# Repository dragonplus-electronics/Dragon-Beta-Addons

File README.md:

# Dragon-Beta Add-ons
Add-on boards by Phill Harvey-Smith for ease of use and construction today.

## Background
The Dragon Beta was a machine in development at the time of Dragon Data's demise in 1984. Only three boards are known to have existed - and only one can be located now. The one board which remains is in the care of the Dragon Data archive at http://www.dragondata.co.uk. It is this latter board which has formed the basis for this current reverse engineering project. Richard, from the Dragon Data archive had made some very clear photographs of his Dragon Beta board before, during and after it's restoration. That board was returned to working order, but understandably Richard was not keen to continually use such a rare piece of computing history. The board was apparently rescued by the Dragon Data M.D. as he left the building for the final time. The Dragon Beta disks were still held by Duncan Smeed of 'Inside the Dragon' fame, and he supplied those to Richard for imaging.

## Improvements and Addons

Many of the components used on the Dragon Beta are obsolete - to the point of being almost unobtainable. Phill has gone to great lengths to create some good add-on boards which can be used to replace the archaic SRAM chips that handle paging, as well as replacing the 32 DRAM chips which provided the original 256K. These are replaced by a small daughterboard. He has also created a 512KB expansion RAM which plugs into the expansion port and effectively takes the machine to 768K of RAM.

Another archaic part of the Beta was its use of the original Sony 26-pin floppy drive connector. This is different to the Amstrad 26-pin connector. Phill has put together a 26-pin to 34-pin adapter, which allows the connection of normal floppy disk drives.

The last area for now is improvements to the keyboard interface. The original Dragon Beta used a matrix scanned/bit serialised keyboard. As with many other old machines, Phill put together a PS/2 keyboard adapter, and in addition now has a USB keyboard and mouse adapter (yes, the Dragon Beta had a mouse - it also had a light pen - but we will likely leave that back in 1984!)

## Disclaimer

These boards have been built and tested and proven to work so far as testing that has been carried out has shown. No warranty is given regarding the suitability or reliability of these boards, and as such, they are supplied as-is for your enjoyment. Any feedback is always welcome.

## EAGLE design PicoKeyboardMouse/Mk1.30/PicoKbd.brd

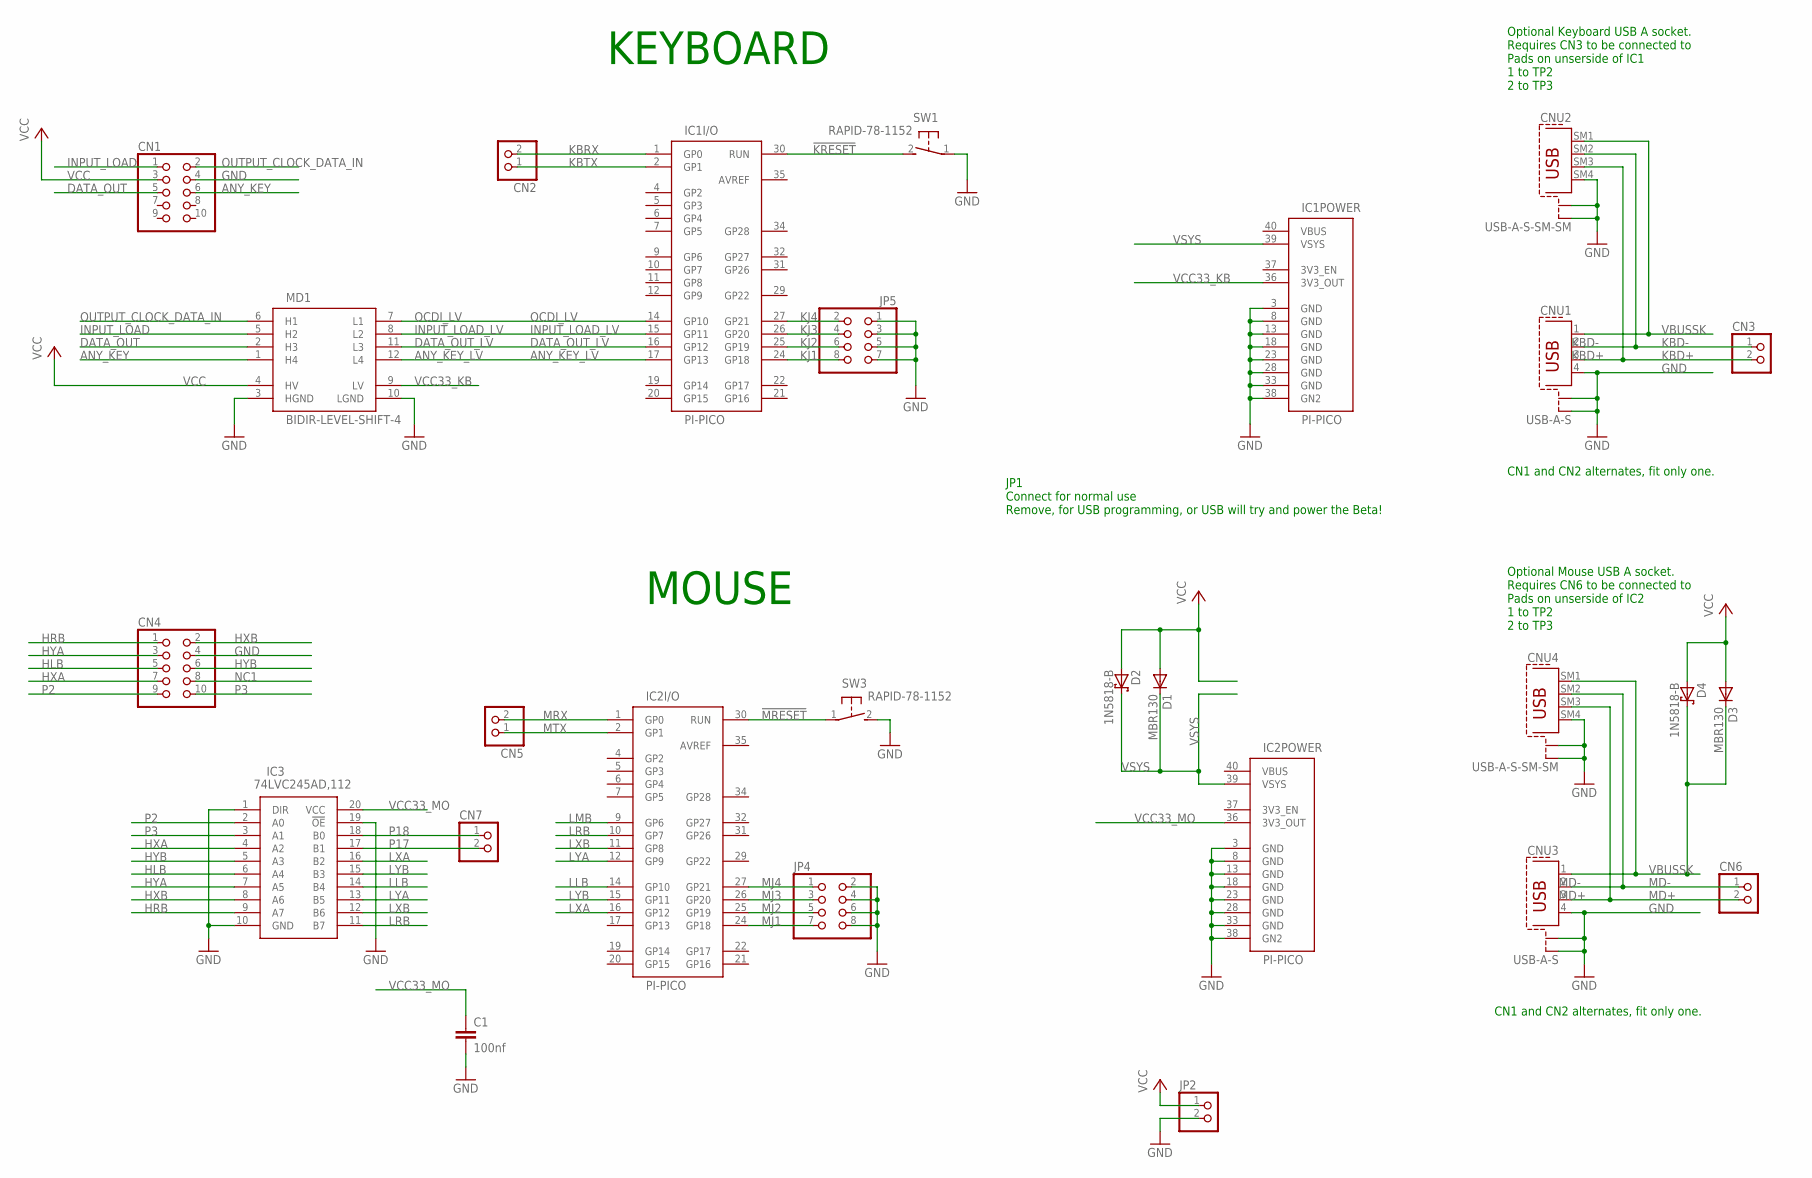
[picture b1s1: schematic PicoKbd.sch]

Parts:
C1: 100nf; C025-025X050
CN1, CN4: PINHD-2X5/90; 2X05/90
CN2, CN3, CN5, CN6, CN7: PINHD-1X2; 1X02
CNU1, CNU3: USB-A-S; USB-A-SHIELD-PTH
CNU2, CNU4: USB-A-S-SM-SM; USB-A-SHIELD-SM
D1, D3: MBR130; SOD123
D2, D4: 1N5818-B; DO41-7.6
IC1, IC2: PI-PICO; PI-PICO-MAIN
IC3: 74LVC245AD,112; SOIC127P1032X265-20N
JP2: PINHD-1X2/90; 1X02/90
JP4, JP5: PINHD-2X4; 2X04
MD1: BIDIR-LEVEL-SHIFT-4; BIDIR-LEVEL-SHIFT
SW1, SW3: RAPID-78-1152; B3F-31XX

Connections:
!KRESET: IC1.30 (RUN), SW1.2 (S)
!MRESET: IC2.30 (RUN), SW3.1
ANY_KEY: CN1.6, MD1.1 (H4)
ANY_KEY_LV: IC1.17 (GP13), MD1.12 (L4)
DATA_OUT: CN1.5, MD1.2 (H3)
DATA_OUT_LV: IC1.16 (GP12), MD1.11 (L3)
GND: C1.2, CN1.4, CN4.4, CNU1.4, CNU1.S1, CNU1.S2, CNU2.S1, CNU2.S2, CNU2.SM4 (4), CNU3.4, CNU3.S1, CNU3.S2, CNU4.S1, CNU4.S2, CNU4.SM4 (4), IC1.3 (GND), IC1.8 (GND), IC1.13 (GND), IC1.18 (GND), IC1.23 (GND), IC1.28 (GND), IC1.33 (GND), IC1.38 (GN2), IC2.3 (GND), IC2.8 (GND), IC2.13 (GND), IC2.18 (GND), IC2.23 (GND), IC2.28 (GND), IC2.33 (GND), IC2.38 (GN2), IC3.1 (DIR), IC3.10 (GND), IC3.19 (!OE), JP2.2, JP4.2, JP4.4, JP4.6, JP4.8, JP5.1, JP5.3, JP5.5, JP5.7, MD1.3 (HGND), MD1.10 (LGND), SW1.1, SW3.2 (S)
HLB: CN4.5, IC3.6 (A4)
HRB: CN4.1, IC3.9 (A7)
HXA: CN4.7, IC3.4 (A2)
HXB: CN4.2, IC3.8 (A6)
HYA: CN4.3, IC3.7 (A5)
HYB: CN4.6, IC3.5 (A3)
INPUT_LOAD: CN1.1, MD1.5 (H2)
INPUT_LOAD_LV: IC1.15 (GP11), MD1.8 (L2)
KBD+: CN3.2, CNU1.3, CNU2.SM3 (3)
KBD-: CN3.1, CNU1.2, CNU2.SM2 (2)
KBRX: CN2.2, IC1.1 (GP0)
KBTX: CN2.1, IC1.2 (GP1)
KJ1: IC1.24 (GP18), JP5.8
KJ2: IC1.25 (GP19), JP5.6
KJ3: IC1.26 (GP20), JP5.4
KJ4: IC1.27 (GP21), JP5.2
LLB: IC2.14 (GP10), IC3.14 (B4)
LMB: IC2.9 (GP6)
LRB: IC2.10 (GP7), IC3.11 (B7)
LXA: IC2.16 (GP12), IC3.16 (B2)
LXB: IC2.11 (GP8), IC3.12 (B6)
LYA: IC2.12 (GP9), IC3.13 (B5)
LYB: IC2.15 (GP11), IC3.15 (B3)
MD+: CN6.2, CNU3.3, CNU4.SM3 (3)
MD-: CN6.1, CNU3.2, CNU4.SM2 (2)
MJ1: IC2.24 (GP18), JP4.7
MJ2: IC2.25 (GP19), JP4.5
MJ3: IC2.26 (GP20), JP4.3
MJ4: IC2.27 (GP21), JP4.1
MRX: CN5.2, IC2.1 (GP0)
MTX: CN5.1, IC2.2 (GP1)
NC1: CN4.8
OCDI_LV: IC1.14 (GP10), MD1.7 (L1)
OUTPUT_CLOCK_DATA_IN: CN1.2, MD1.6 (H1)
P2: CN4.9, IC3.2 (A0)
P3: CN4.10, IC3.3 (A1)
P17: CN7.2, IC3.17 (B1)
P18: CN7.1, IC3.18 (B0)
VBUSSK: CNU1.1, CNU2.SM1 (1), CNU3.1, CNU4.SM1 (1), D3.C, D4.C
VCC: CN1.3, D1.A, D2.A, D3.A, D4.A, JP2.1, MD1.4 (HV)
VCC33_KB: IC1.36 (3V3_OUT), MD1.9 (LV)
VCC33_MO: C1.1, IC2.36 (3V3_OUT), IC3.20 (VCC)
VSYS: D1.C, D2.C, IC1.39 (VSYS), IC2.39 (VSYS)

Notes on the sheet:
JP1 Connect for normal use Remove, for USB programming, or USB will try and power the Beta!
KEYBOARD
MOUSE
CN1 and CN2 alternates, fit only one.
Optional Keyboard USB A socket. Requires CN3 to be connected to Pads on unserside of IC1 1 to TP2 2 to TP3
Optional Mouse USB A socket. Requires CN6 to be connected to Pads on unserside of IC2 1 to TP2 2 to TP3

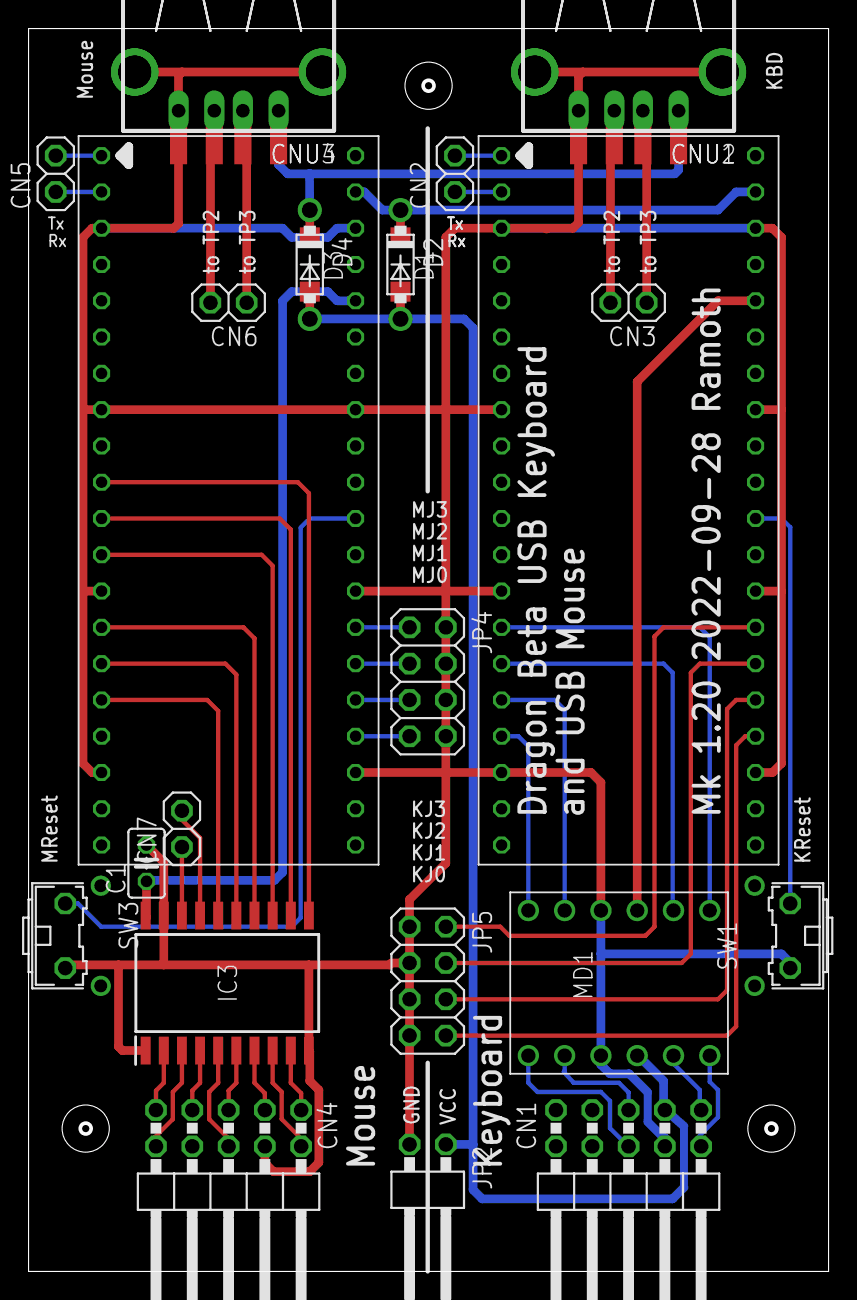
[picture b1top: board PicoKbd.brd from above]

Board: 2 copper layers, 55.7 x 86.7 mm, 28 parts (0 on the bottom side), 48 nets.

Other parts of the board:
U$1, U$3, U$4: STAND-OFF

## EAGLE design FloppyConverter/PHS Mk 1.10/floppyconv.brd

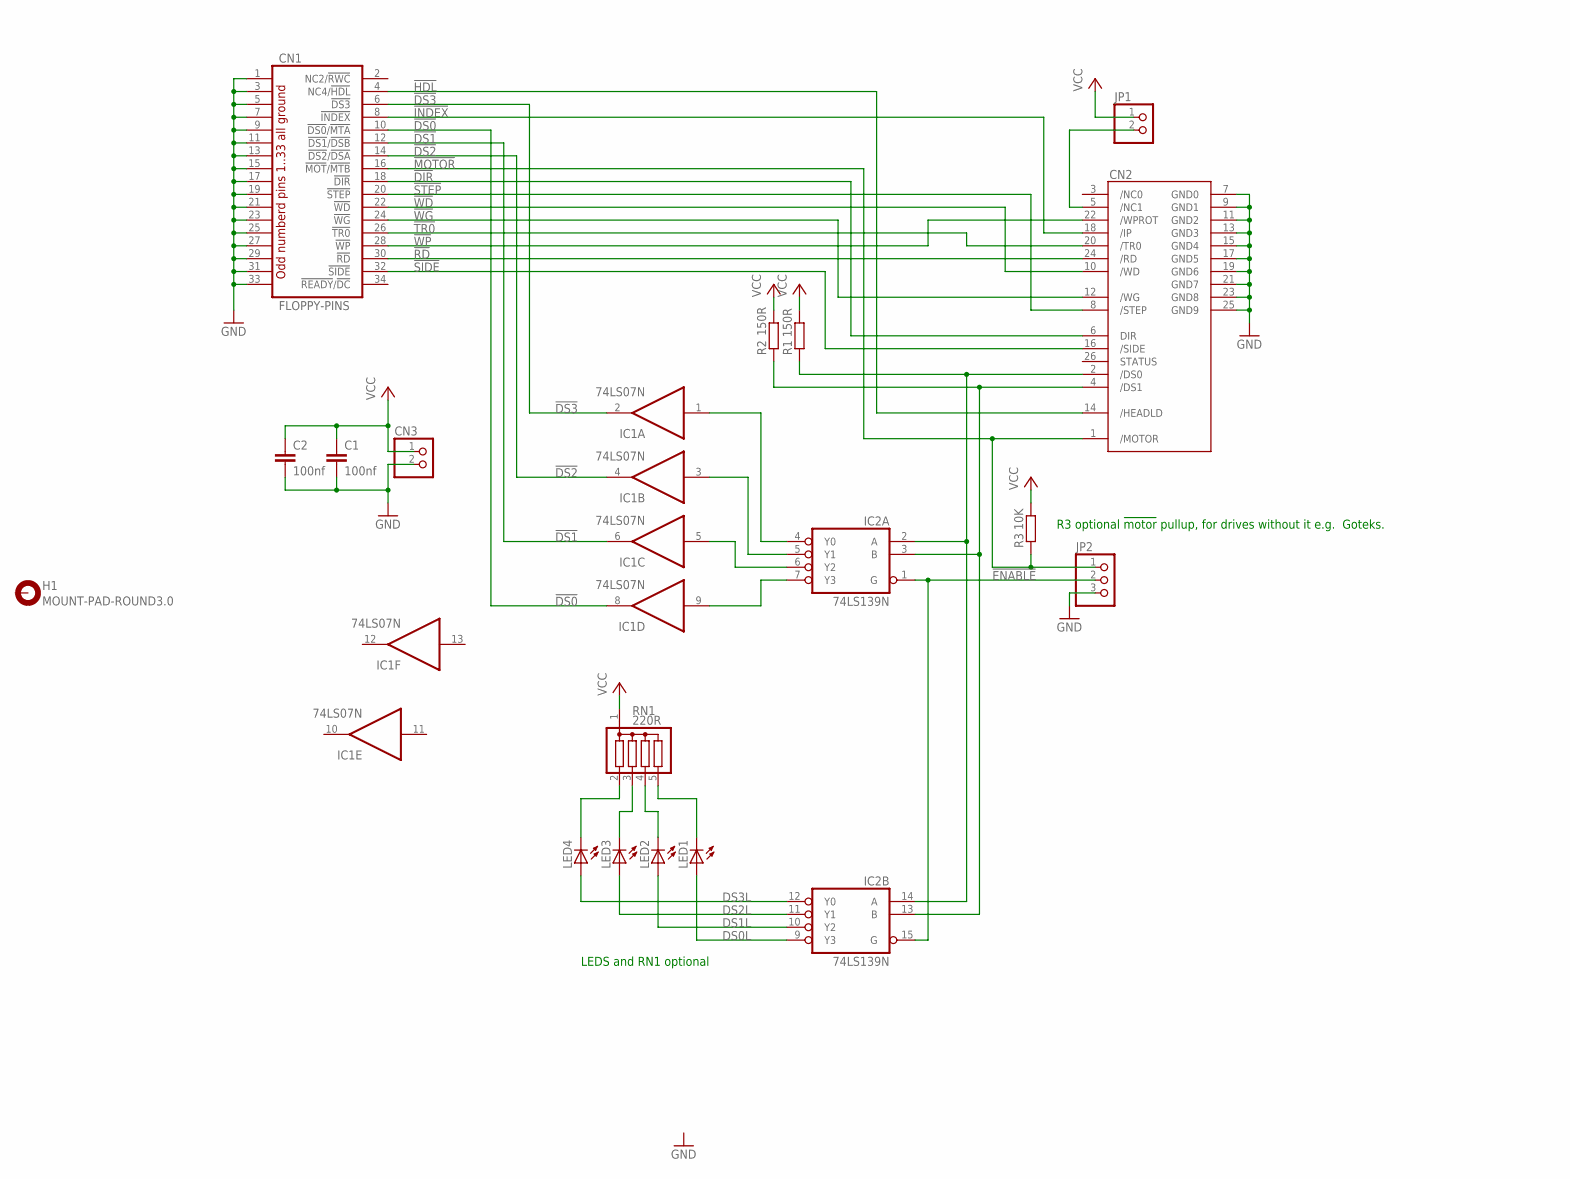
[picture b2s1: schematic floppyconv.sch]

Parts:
C1, C2: 100nf; C025-025X050
CN1: FLOPPY-PINS
CN2: DRAGON-BETA-FLOPPY; 2X13
CN3: PINHD-1X2; 1X02
H1: MOUNT-PAD-ROUND3.0; 3,0-PAD
IC1: 74LS07N; DIL14
IC2: 74LS139N; DIL16
JP1: PINHD-1X2; 1X02
JP2: PINHD-1X3; 1X03
LED1, LED2, LED3, LED4: LED3MM
R1, R2: 150R; 0207/10
R3: 10K; 0207/10
RN1: 220R; SIL5R

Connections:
!BDS0: CN2.2 (/DS0), IC2.2 (A), IC2.14 (A), R1.1
!BDS1: CN2.4 (/DS1), IC2.3 (B), IC2.13 (B), R2.1
!DIR: CN1.18 (!DIR), CN2.6 (DIR)
!DS0: CN1.10 (!DS0!/!MTA), IC1.8 (O)
!DS1: CN1.12 (!DS1!/!DSB), IC1.6 (O)
!DS2: CN1.14 (!DS2!/!DSA), IC1.4 (O)
!DS3: CN1.6 (!DS3), IC1.2 (O)
!ENABLE: IC2.1 (G), IC2.15 (G), JP2.2
!HDL: CN1.4 (NC4/!HDL), CN2.14 (/HEADLD)
!INDEX: CN1.8 (!INDEX), CN2.18 (/IP)
!MOTOR: CN1.16 (!MOT!/!MTB), CN2.1 (/MOTOR), JP2.1, R3.1
!RD: CN1.30 (!RD), CN2.24 (/RD)
!SIDE: CN1.32 (!SIDE), CN2.16 (/SIDE)
!STEP: CN1.20 (!STEP), CN2.8 (/STEP)
!TR0: CN1.26 (!TR0), CN2.20 (/TR0)
!WD: CN1.22 (!WD), CN2.10 (/WD)
!WG: CN1.24 (!WG), CN2.12 (/WG)
!WP: CN1.28 (!WP), CN2.22 (/WPROT)
DS0L: IC2.9 (Y3), LED1.A
DS1L: IC2.10 (Y2), LED2.A
DS2L: IC2.11 (Y1), LED3.A
DS3L: IC2.12 (Y0), LED4.A
GND: C1.2, C2.2, CN1.1 (GND), CN1.3 (GND), CN1.5 (GND), CN1.7 (GND), CN1.9 (GND), CN1.11 (GND), CN1.13 (GND), CN1.15 (GND), CN1.17 (GND), CN1.19 (GND), CN1.21 (GND), CN1.23 (GND), CN1.25 (GND), CN1.27 (GND), CN1.29 (GND), CN1.31 (GND), CN1.33 (GND), CN2.7 (GND0), CN2.9 (GND1), CN2.11 (GND2), CN2.13 (GND3), CN2.15 (GND4), CN2.17 (GND5), CN2.19 (GND6), CN2.21 (GND7), CN2.23 (GND8), CN2.25 (GND9), CN3.2, IC1.7 (GND), IC2.8 (GND), JP2.3
unnamed: IC1.1 (I), IC2.4 (Y0)
unnamed: IC1.3 (I), IC2.5 (Y1)
unnamed: IC1.5 (I), IC2.6 (Y2)
unnamed: IC1.9 (I), IC2.7 (Y3)
unnamed: LED1.K (C), RN1.5
unnamed: LED2.K (C), RN1.4
unnamed: LED3.K (C), RN1.3
unnamed: LED4.K (C), RN1.2
unnamed: CN2.5 (/NC1), JP1.2
VCC: C1.1, C2.1, CN3.1, IC1.14 (VCC), IC2.16 (VCC), JP1.1, R1.2, R2.2, R3.2, RN1.1

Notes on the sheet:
LEDS and RN1 optional
R3 optional !motor! pullup, for drives without it e.g. Goteks.

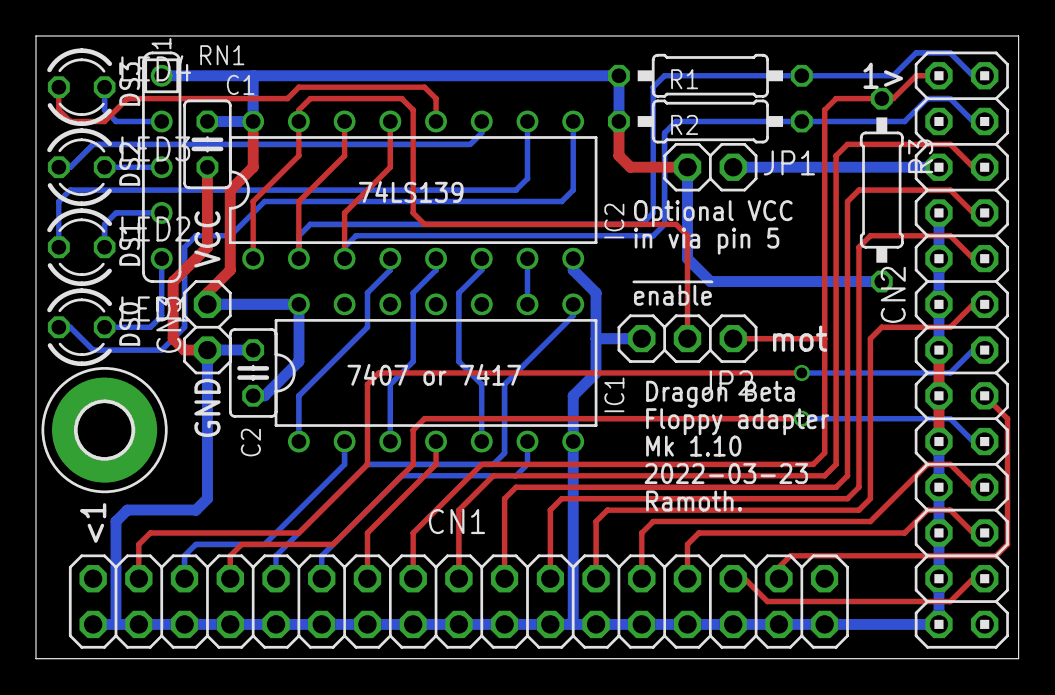
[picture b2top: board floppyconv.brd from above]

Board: 2 copper layers, 54.6 x 34.6 mm, 18 parts (0 on the bottom side), 33 nets.

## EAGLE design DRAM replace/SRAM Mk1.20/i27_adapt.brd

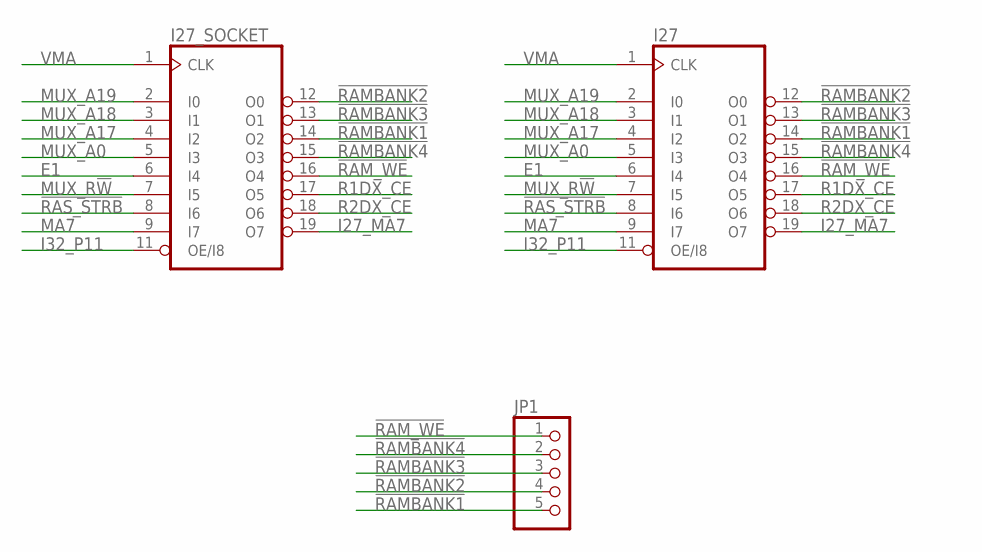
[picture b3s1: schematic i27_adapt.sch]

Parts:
I27, I27_SOCKET: 16V8-ROUND; DIL20-R
JP1: PINHD-1X5/90; 1X05/90

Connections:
!RAMBANK1: I27.14 (O2), I27_SOCKET.14 (O2), JP1.5
!RAMBANK2: I27.12 (O0), I27_SOCKET.12 (O0), JP1.4
!RAMBANK3: I27.13 (O1), I27_SOCKET.13 (O1), JP1.3
!RAMBANK4: I27.15 (O3), I27_SOCKET.15 (O3), JP1.2
!RAM_WE: I27.16 (O4), I27_SOCKET.16 (O4), JP1.1
!RAS_STRB: I27.8 (I6), I27_SOCKET.8 (I6)
E1: I27.6 (I4), I27_SOCKET.6 (I4)
GND: I27.10 (GND), I27_SOCKET.10 (GND)
I27_MA7: I27.19 (O7), I27_SOCKET.19 (O7)
I32_P11: I27.11 (OE/I8), I27_SOCKET.11 (OE/I8)
MA7: I27.9 (I7), I27_SOCKET.9 (I7)
MUX_A0: I27.5 (I3), I27_SOCKET.5 (I3)
MUX_A17: I27.4 (I2), I27_SOCKET.4 (I2)
MUX_A18: I27.3 (I1), I27_SOCKET.3 (I1)
MUX_A19: I27.2 (I0), I27_SOCKET.2 (I0)
MUX_R!W!: I27.7 (I5), I27_SOCKET.7 (I5)
R1DX_CE: I27.17 (O5), I27_SOCKET.17 (O5)
R2DX_CE: I27.18 (O6), I27_SOCKET.18 (O6)
VCC: I27.20 (VCC), I27_SOCKET.20 (VCC)
VMA: I27.1 (CLK), I27_SOCKET.1 (CLK)

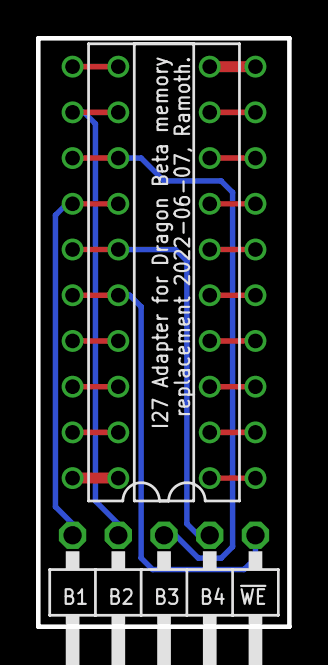
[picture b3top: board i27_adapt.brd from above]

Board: 2 copper layers, 13.9 x 32.7 mm, 3 parts (0 on the bottom side), 20 nets.

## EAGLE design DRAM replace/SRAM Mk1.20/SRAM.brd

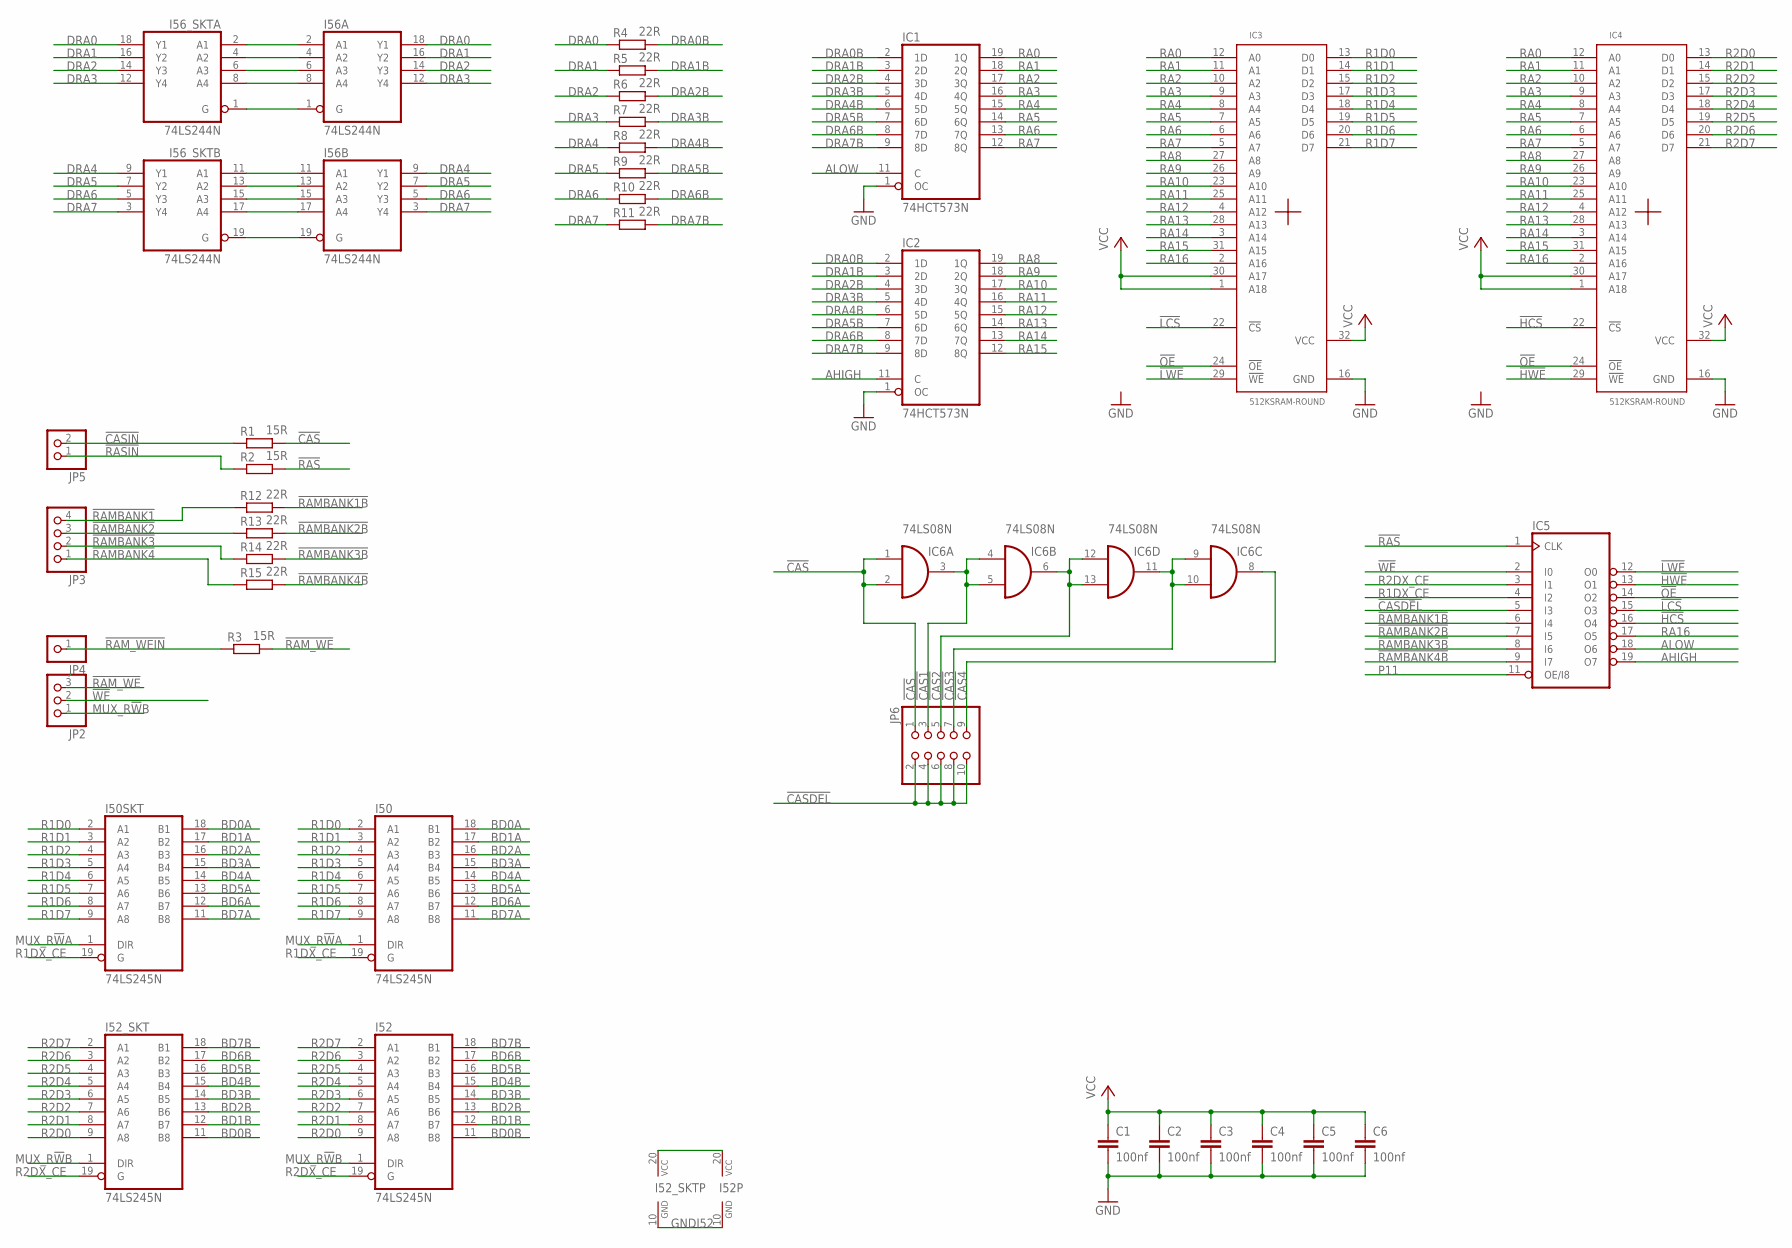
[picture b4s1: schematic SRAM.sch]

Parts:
C1, C2, C3, C4, C5, C6: 100nf; C025-025X050
I50, I50SKT, I52, I52_SKT: 74LS245N; DIL20
I56, I56_SKT: 74LS244N; DIL20
IC1, IC2: 74HCT573N; DIL20
IC3, IC4: 512KSRAM-ROUND; DIL32-ROUND
IC5: 16V8-ROUND; DIL20-R
IC6: 74LS08N; DIL14
JP2: PINHD-1X3; 1X03
JP3: PINHD-1X4; 1X04
JP4: PINHD-1X1; 1X01
JP5: PINHD-1X2; 1X02
JP6: PINHD-2X5; 2X05
R1, R2, R3: 15R; 0204/5
R4, R5, R6, R7, R8, R9, R10, R11, R12, R13, R14, R15: 22R; 0204/5

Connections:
!CAS: IC6.1 (I0), IC6.2 (I1), JP6.1, R1.2
!CAS1: IC6.3 (O), IC6.4 (I0), IC6.5 (I1), JP6.3
!CAS2: IC6.6 (O), IC6.12 (I0), IC6.13 (I1), JP6.5
!CAS3: IC6.9 (I0), IC6.10 (I1), IC6.11 (O), JP6.7
!CAS4: IC6.8 (O), JP6.9
!CASDEL: IC5.5 (I3), JP6.2, JP6.4, JP6.6, JP6.8, JP6.10
!CASIN: JP5.2, R1.1
!HCS: IC4.22 (!CS), IC5.16 (O4)
!HWE: IC4.29 (!WE), IC5.13 (O1)
!LCS: IC3.22 (!CS), IC5.15 (O3)
!LWE: IC3.29 (!WE), IC5.12 (O0)
!OE: IC3.24 (!OE), IC4.24 (!OE), IC5.14 (O2)
!RAMBANK1: JP3.4, R12.1
!RAMBANK1B: IC5.6 (I4), R12.2
!RAMBANK2: JP3.3, R13.1
!RAMBANK2B: IC5.7 (I5), R13.2
!RAMBANK3: JP3.2, R14.1
!RAMBANK3B: IC5.8 (I6), R14.2
!RAMBANK4: JP3.1, R15.1
!RAMBANK4B: IC5.9 (I7), R15.2
!RAM_WE: JP2.3, R3.2
!RAM_WEIN: JP4.1, R3.1
!RAS: IC5.1 (CLK), R2.2
!RASIN: JP5.1, R2.1
!WE: IC5.2 (I0), JP2.2
AHIGH: IC2.11 (C), IC5.19 (O7)
ALOW: IC1.11 (C), IC5.18 (O6)
BD0A: I50.18 (B1), I50SKT.18 (B1)
BD0B: I52.11 (B8), I52_SKT.11 (B8)
BD1A: I50.17 (B2), I50SKT.17 (B2)
BD1B: I52.12 (B7), I52_SKT.12 (B7)
BD2A: I50.16 (B3), I50SKT.16 (B3)
BD2B: I52.13 (B6), I52_SKT.13 (B6)
BD3A: I50.15 (B4), I50SKT.15 (B4)
BD3B: I52.14 (B5), I52_SKT.14 (B5)
BD4A: I50.14 (B5), I50SKT.14 (B5)
BD4B: I52.15 (B4), I52_SKT.15 (B4)
BD5A: I50.13 (B6), I50SKT.13 (B6)
BD5B: I52.16 (B3), I52_SKT.16 (B3)
BD6A: I50.12 (B7), I50SKT.12 (B7)
BD6B: I52.17 (B2), I52_SKT.17 (B2)
BD7A: I50.11 (B8), I50SKT.11 (B8)
BD7B: I52.18 (B1), I52_SKT.18 (B1)
DRA0: I56.18 (Y1), I56_SKT.18 (Y1), R4.1
DRA0B: IC1.2 (1D), IC2.2 (1D), R4.2
DRA1: I56.16 (Y2), I56_SKT.16 (Y2), R5.1
DRA1B: IC1.3 (2D), IC2.3 (2D), R5.2
DRA2: I56.14 (Y3), I56_SKT.14 (Y3), R6.1
DRA2B: IC1.4 (3D), IC2.4 (3D), R6.2
DRA3: I56.12 (Y4), I56_SKT.12 (Y4), R7.1
DRA3B: IC1.5 (4D), IC2.5 (4D), R7.2
DRA4: I56.9 (Y1), I56_SKT.9 (Y1), R8.1
DRA4B: IC1.6 (5D), IC2.6 (5D), R8.2
DRA5: I56.7 (Y2), I56_SKT.7 (Y2), R9.1
DRA5B: IC1.7 (6D), IC2.7 (6D), R9.2
DRA6: I56.5 (Y3), I56_SKT.5 (Y3), R10.1
DRA6B: IC1.8 (7D), IC2.8 (7D), R10.2
DRA7: I56.3 (Y4), I56_SKT.3 (Y4), R11.1
DRA7B: IC1.9 (8D), IC2.9 (8D), R11.2
GND: C1.2, C2.2, C3.2, C4.2, C5.2, C6.2, I50.10 (GND), I50SKT.10 (GND), I56.10 (GND), I56_SKT.10 (GND), IC1.1 (OC), IC1.10 (GND), IC2.1 (OC), IC2.10 (GND), IC3.16 (GND), IC4.16 (GND), IC5.10 (GND), IC6.7 (GND)
GNDI52: I52.10 (GND), I52_SKT.10 (GND)
MUX_R!W!A: I50.1 (DIR), I50SKT.1 (DIR)
MUX_R!W!B: I52.1 (DIR), I52_SKT.1 (DIR), JP2.1
unnamed: I56.11 (A1), I56_SKT.11 (A1)
unnamed: I56.13 (A2), I56_SKT.13 (A2)
unnamed: I56.15 (A3), I56_SKT.15 (A3)
unnamed: I56.17 (A4), I56_SKT.17 (A4)
unnamed: I56.19 (G), I56_SKT.19 (G)
unnamed: I56.1 (G), I56_SKT.1 (G)
unnamed: I56.8 (A4), I56_SKT.8 (A4)
unnamed: I56.6 (A3), I56_SKT.6 (A3)
unnamed: I56.4 (A2), I56_SKT.4 (A2)
unnamed: I56.2 (A1), I56_SKT.2 (A1)
P11: IC5.11 (OE/I8)
R1D0: I50.2 (A1), I50SKT.2 (A1), IC3.13 (D0)
R1D1: I50.3 (A2), I50SKT.3 (A2), IC3.14 (D1)
R1D2: I50.4 (A3), I50SKT.4 (A3), IC3.15 (D2)
R1D3: I50.5 (A4), I50SKT.5 (A4), IC3.17 (D3)
R1D4: I50.6 (A5), I50SKT.6 (A5), IC3.18 (D4)
R1D5: I50.7 (A6), I50SKT.7 (A6), IC3.19 (D5)
R1D6: I50.8 (A7), I50SKT.8 (A7), IC3.20 (D6)
R1D7: I50.9 (A8), I50SKT.9 (A8), IC3.21 (D7)
R1DX_CE: I50.19 (G), I50SKT.19 (G), IC5.4 (I2)
R2D0: I52.9 (A8), I52_SKT.9 (A8), IC4.13 (D0)
R2D1: I52.8 (A7), I52_SKT.8 (A7), IC4.14 (D1)
R2D2: I52.7 (A6), I52_SKT.7 (A6), IC4.15 (D2)
R2D3: I52.6 (A5), I52_SKT.6 (A5), IC4.17 (D3)
R2D4: I52.5 (A4), I52_SKT.5 (A4), IC4.18 (D4)
R2D5: I52.4 (A3), I52_SKT.4 (A3), IC4.19 (D5)
R2D6: I52.3 (A2), I52_SKT.3 (A2), IC4.20 (D6)
R2D7: I52.2 (A1), I52_SKT.2 (A1), IC4.21 (D7)
R2DX_CE: I52.19 (G), I52_SKT.19 (G), IC5.3 (I1)
RA0: IC1.19 (1Q), IC3.12 (A0), IC4.12 (A0)
RA1: IC1.18 (2Q), IC3.11 (A1), IC4.11 (A1)
RA2: IC1.17 (3Q), IC3.10 (A2), IC4.10 (A2)
RA3: IC1.16 (4Q), IC3.9 (A3), IC4.9 (A3)
RA4: IC1.15 (5Q), IC3.8 (A4), IC4.8 (A4)
RA5: IC1.14 (6Q), IC3.7 (A5), IC4.7 (A5)
RA6: IC1.13 (7Q), IC3.6 (A6), IC4.6 (A6)
RA7: IC1.12 (8Q), IC3.5 (A7), IC4.5 (A7)
RA8: IC2.19 (1Q), IC3.27 (A8), IC4.27 (A8)
RA9: IC2.18 (2Q), IC3.26 (A9), IC4.26 (A9)
RA10: IC2.17 (3Q), IC3.23 (A10), IC4.23 (A10)
RA11: IC2.16 (4Q), IC3.25 (A11), IC4.25 (A11)
RA12: IC2.15 (5Q), IC3.4 (A12), IC4.4 (A12)
RA13: IC2.14 (6Q), IC3.28 (A13), IC4.28 (A13)
RA14: IC2.13 (7Q), IC3.3 (A14), IC4.3 (A14)
RA15: IC2.12 (8Q), IC3.31 (A15), IC4.31 (A15)
RA16: IC3.2 (A16), IC4.2 (A16), IC5.17 (O5)
VCC: C1.1, C2.1, C3.1, C4.1, C5.1, C6.1, I50.20 (VCC), I50SKT.20 (VCC), I56.20 (VCC), I56_SKT.20 (VCC), IC1.20 (VCC), IC2.20 (VCC), IC3.1 (A18), IC3.30 (A17), IC3.32 (VCC), IC4.1 (A18), IC4.30 (A17), IC4.32 (VCC), IC5.20 (VCC), IC6.14 (VCC)
VCCI52: I52.20 (VCC), I52_SKT.20 (VCC)

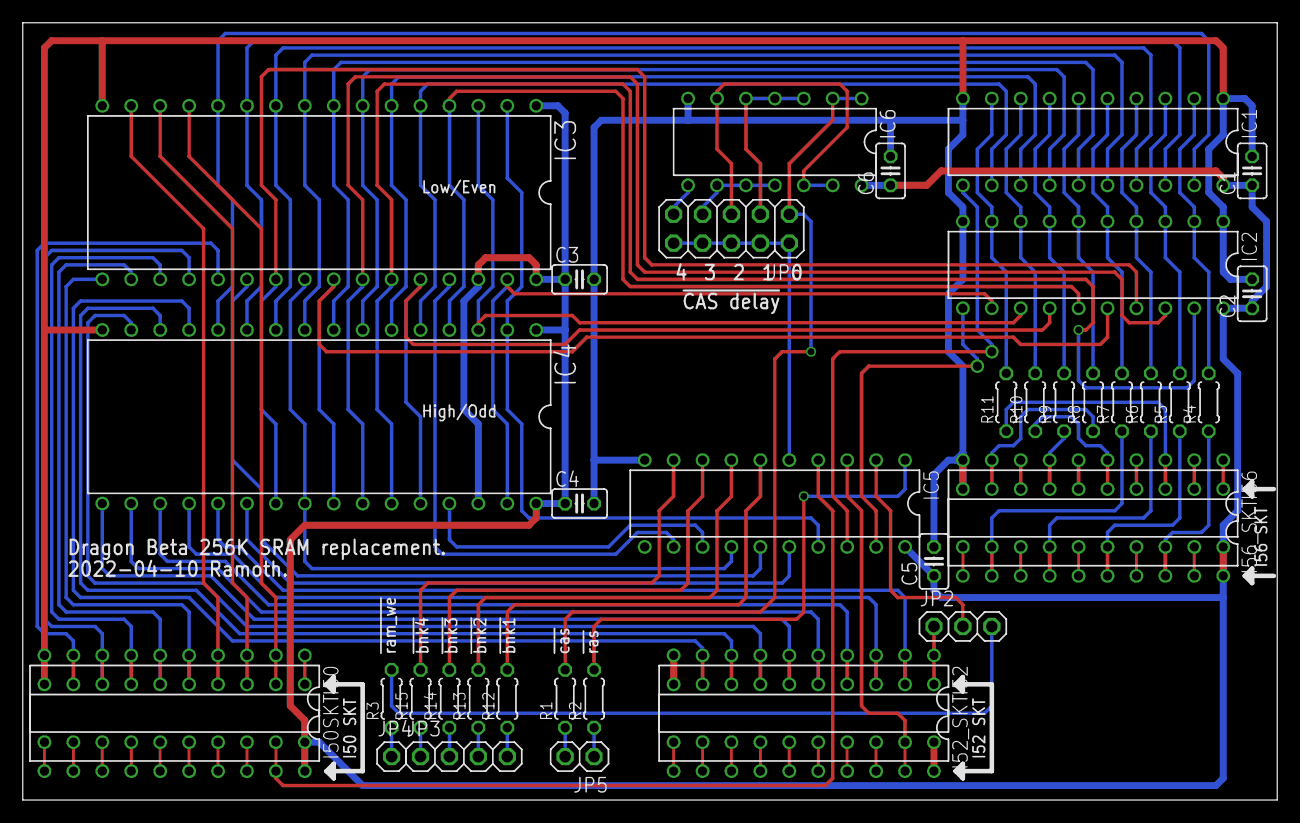
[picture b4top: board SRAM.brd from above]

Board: 2 copper layers, 110.2 x 68.2 mm, 38 parts (0 on the bottom side), 110 nets.

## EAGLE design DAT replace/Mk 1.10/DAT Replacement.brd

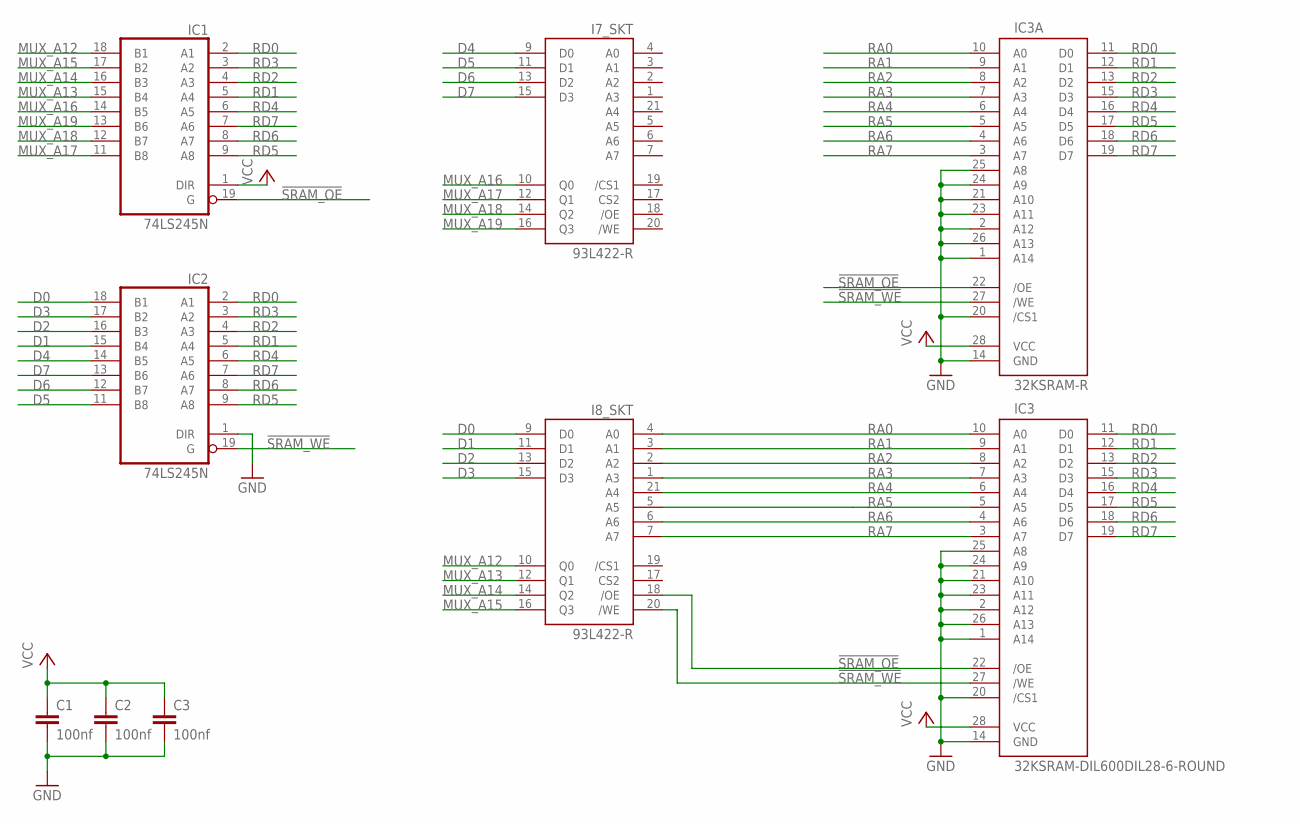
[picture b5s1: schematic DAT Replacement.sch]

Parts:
C1, C2, C3: 100nf; C025-025X050
I7_SKT, I8_SKT: 93L422-R; DIL-22-4-ROUND
IC1, IC2: 74LS245N; DIL20
IC3: 32KSRAM-DIL600DIL28-6-ROUND; DIL28-6-ROUND
IC3A: 32KSRAM-R; DIL28-3-ROUND

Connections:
!SRAM_OE: I8_SKT.18 (/OE), IC1.19 (G), IC3.22 (/OE), IC3A.22 (/OE)
!SRAM_WE: I8_SKT.20 (/WE), IC2.19 (G), IC3.27 (/WE), IC3A.27 (/WE)
D0: I8_SKT.9 (D0), IC2.18 (B1)
D1: I8_SKT.11 (D1), IC2.15 (B4)
D2: I8_SKT.13 (D2), IC2.16 (B3)
D3: I8_SKT.15 (D3), IC2.17 (B2)
D4: I7_SKT.9 (D0), IC2.14 (B5)
D5: I7_SKT.11 (D1), IC2.11 (B8)
D6: I7_SKT.13 (D2), IC2.12 (B7)
D7: I7_SKT.15 (D3), IC2.13 (B6)
GND: C1.2, C2.2, C3.2, I7_SKT.8 (GND), I8_SKT.8 (GND), IC1.10 (GND), IC2.1 (DIR), IC2.10 (GND), IC3.1 (A14), IC3.2 (A12), IC3.14 (GND), IC3.20 (/CS1), IC3.21 (A10), IC3.23 (A11), IC3.24 (A9), IC3.25 (A8), IC3.26 (A13), IC3A.1 (A14), IC3A.2 (A12), IC3A.14 (GND), IC3A.20 (/CS1), IC3A.21 (A10), IC3A.23 (A11), IC3A.24 (A9), IC3A.25 (A8), IC3A.26 (A13)
MUX_A12: I8_SKT.10 (Q0), IC1.18 (B1)
MUX_A13: I8_SKT.12 (Q1), IC1.15 (B4)
MUX_A14: I8_SKT.14 (Q2), IC1.16 (B3)
MUX_A15: I8_SKT.16 (Q3), IC1.17 (B2)
MUX_A16: I7_SKT.10 (Q0), IC1.14 (B5)
MUX_A17: I7_SKT.12 (Q1), IC1.11 (B8)
MUX_A18: I7_SKT.14 (Q2), IC1.12 (B7)
MUX_A19: I7_SKT.16 (Q3), IC1.13 (B6)
RA0: I8_SKT.4 (A0), IC3.10 (A0), IC3A.10 (A0)
RA1: I8_SKT.3 (A1), IC3.9 (A1), IC3A.9 (A1)
RA2: I8_SKT.2 (A2), IC3.8 (A2), IC3A.8 (A2)
RA3: I8_SKT.1 (A3), IC3.7 (A3), IC3A.7 (A3)
RA4: I8_SKT.21 (A4), IC3.6 (A4), IC3A.6 (A4)
RA5: I8_SKT.5 (A5), IC3.5 (A5), IC3A.5 (A5)
RA6: I8_SKT.6 (A6), IC3.4 (A6), IC3A.4 (A6)
RA7: I8_SKT.7 (A7), IC3.3 (A7), IC3A.3 (A7)
RD0: IC1.2 (A1), IC2.2 (A1), IC3.11 (D0), IC3A.11 (D0)
RD1: IC1.5 (A4), IC2.5 (A4), IC3.12 (D1), IC3A.12 (D1)
RD2: IC1.4 (A3), IC2.4 (A3), IC3.13 (D2), IC3A.13 (D2)
RD3: IC1.3 (A2), IC2.3 (A2), IC3.15 (D3), IC3A.15 (D3)
RD4: IC1.6 (A5), IC2.6 (A5), IC3.16 (D4), IC3A.16 (D4)
RD5: IC1.9 (A8), IC2.9 (A8), IC3.17 (D5), IC3A.17 (D5)
RD6: IC1.8 (A7), IC2.8 (A7), IC3.18 (D6), IC3A.18 (D6)
RD7: IC1.7 (A6), IC2.7 (A6), IC3.19 (D7), IC3A.19 (D7)
VCC: C1.1, C2.1, C3.1, I7_SKT.22 (VCC), I8_SKT.22 (VCC), IC1.1 (DIR), IC1.20 (VCC), IC2.20 (VCC), IC3.28 (VCC), IC3A.28 (VCC)

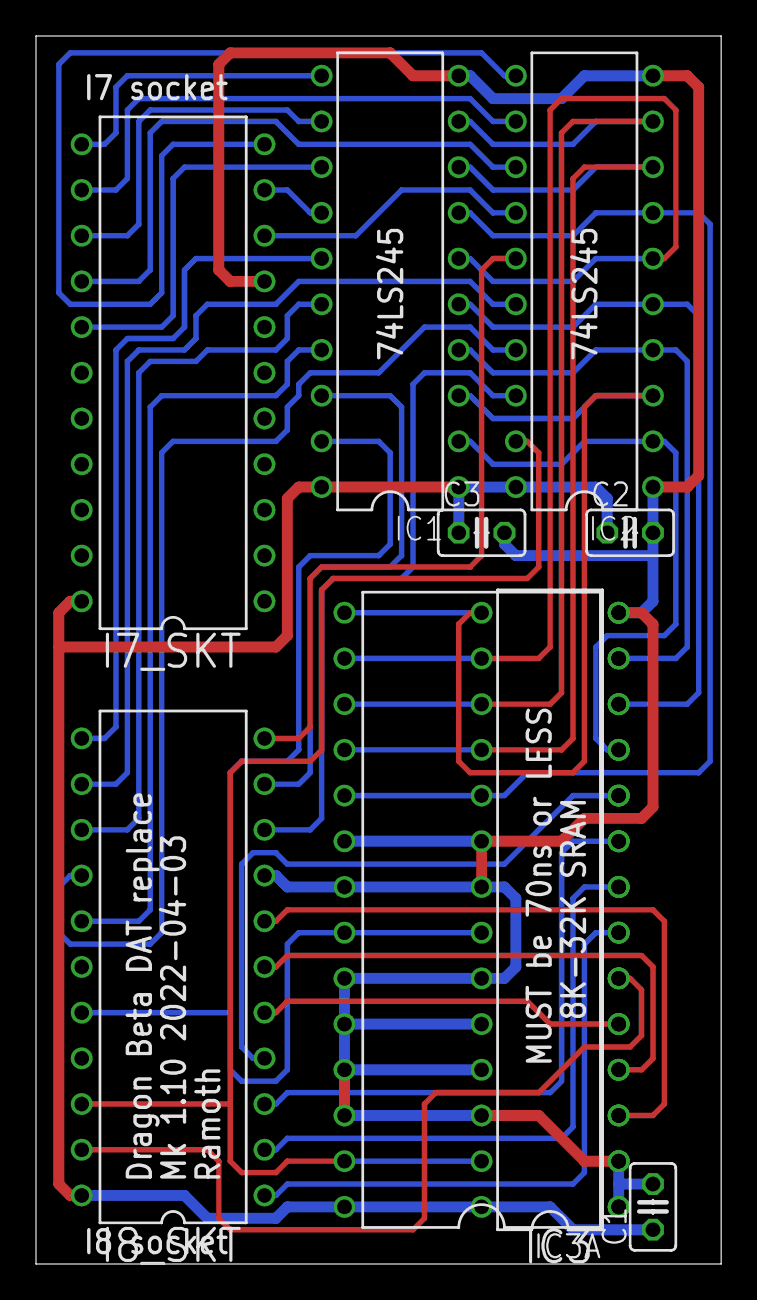
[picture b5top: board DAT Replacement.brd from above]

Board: 2 copper layers, 38.1 x 68.2 mm, 9 parts (0 on the bottom side), 36 nets.

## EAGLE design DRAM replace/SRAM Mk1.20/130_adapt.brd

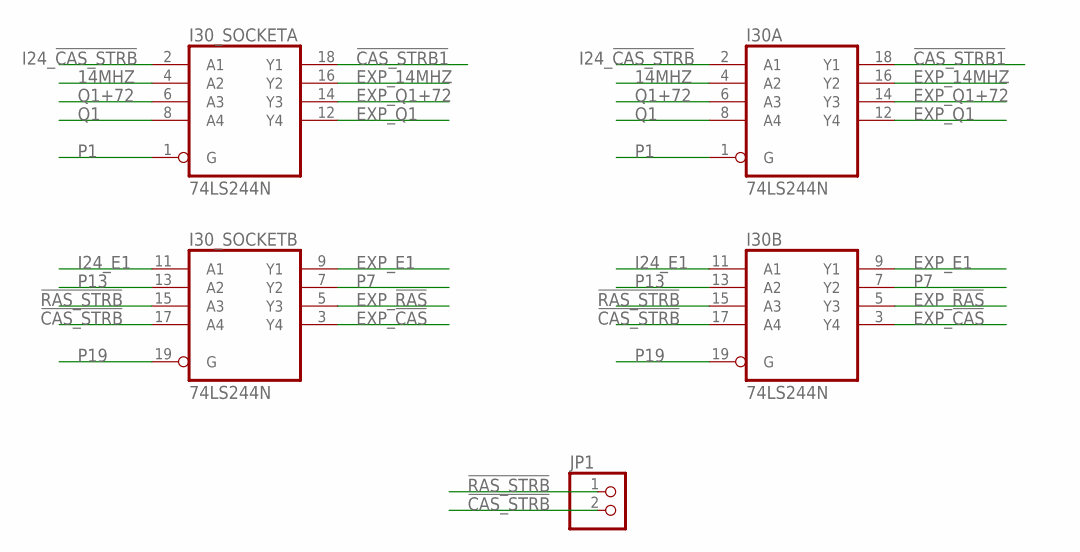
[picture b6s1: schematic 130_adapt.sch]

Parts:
I30, I30_SOCKET: 74LS244N; DIL20
JP1: PINHD-1X2/90; 1X02/90

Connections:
14MHZ: I30.4 (A2), I30_SOCKET.4 (A2)
!CAS_STRB: I30.17 (A4), I30_SOCKET.17 (A4), JP1.2
!CAS_STRB1: I30.18 (Y1), I30_SOCKET.18 (Y1)
!RAS_STRB: I30.15 (A3), I30_SOCKET.15 (A3), JP1.1
EXP_14MHZ: I30.16 (Y2), I30_SOCKET.16 (Y2)
EXP_!CAS: I30.3 (Y4), I30_SOCKET.3 (Y4)
EXP_!RAS: I30.5 (Y3), I30_SOCKET.5 (Y3)
EXP_E1: I30.9 (Y1), I30_SOCKET.9 (Y1)
EXP_Q1: I30.12 (Y4), I30_SOCKET.12 (Y4)
EXP_Q1+72: I30.14 (Y3), I30_SOCKET.14 (Y3)
GND: I30.10 (GND), I30_SOCKET.10 (GND)
I24_!CAS_STRB: I30.2 (A1), I30_SOCKET.2 (A1)
I24_E1: I30.11 (A1), I30_SOCKET.11 (A1)
P1: I30.1 (G), I30_SOCKET.1 (G)
P7: I30.7 (Y2), I30_SOCKET.7 (Y2)
P13: I30.13 (A2), I30_SOCKET.13 (A2)
P19: I30.19 (G), I30_SOCKET.19 (G)
Q1: I30.8 (A4), I30_SOCKET.8 (A4)
Q1+72: I30.6 (A3), I30_SOCKET.6 (A3)
VCC: I30.20 (VCC), I30_SOCKET.20 (VCC)

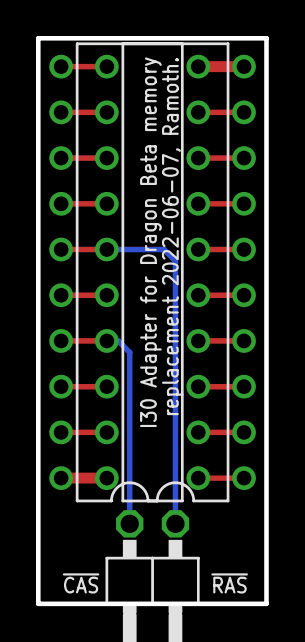
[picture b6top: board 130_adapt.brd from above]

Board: 2 copper layers, 12.7 x 31.4 mm, 3 parts (0 on the bottom side), 20 nets.
